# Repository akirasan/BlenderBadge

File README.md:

# BlenderBadge
Una PCB badge basada en el logo de Blender

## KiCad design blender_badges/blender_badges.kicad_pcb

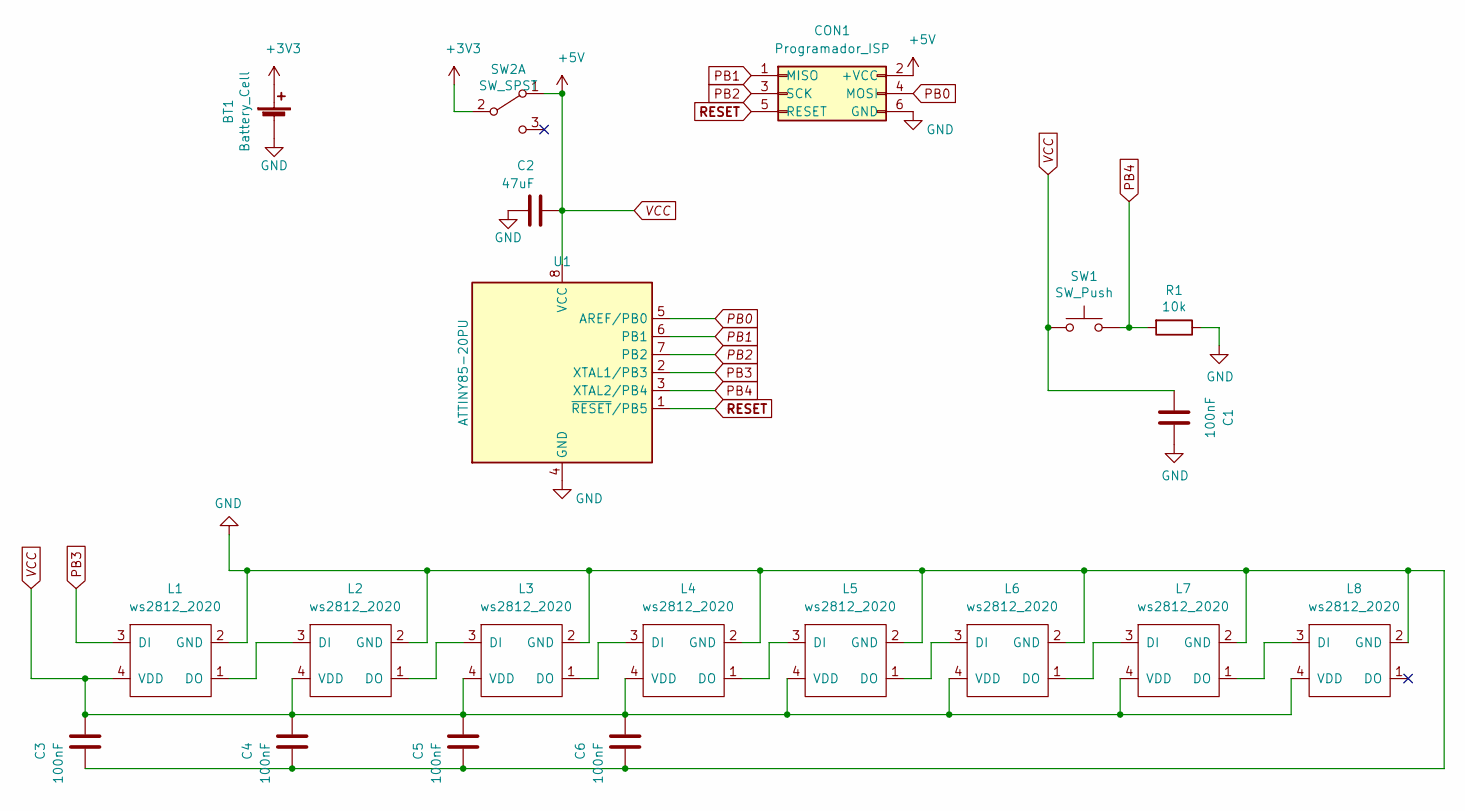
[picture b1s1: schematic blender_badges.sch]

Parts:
BT1: Battery_Cell; BatteryHolder_Keystone_3034_1x20mm_MODIFICADA
C1, C3, C4, C5, C6: 100nF; C_0805_2012Metric_Pad1.15x1.40mm_HandSolder
C2: 47uF; C_0805_2012Metric_Pad1.15x1.40mm_HandSolder
CON1: Programador_ISP; ISP_TestPoints
L1, L2, L3, L4, L5, L6, L7, L8: ws2812_2020
R1: 10k; R_0805_2012Metric_Pad1.15x1.40mm_HandSolder
SW1: SW_Push; SW_SPST_TL3342
SW2: SW_SPST; SWITCH_SPST_SMD_A
U1: ATTINY85-20PU; SOIJ-8_5.3x5.3mm_P1.27mm

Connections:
+3V3: BT1.1 (+), SW2.2 (B)
GND: BT1.2 (-), C1.2, C2.1, C3.1, C4.1, C5.1, C6.1, CON1.6 (GND), L1.2 (GND), L2.2 (GND), L3.2 (GND), L4.2 (GND), L5.2 (GND), L6.2 (GND), L7.2 (GND), L8.2 (GND), R1.1, U1.4 (GND)
unnamed: L1.1 (DO), L2.3 (DI)
unnamed: L2.1 (DO), L3.3 (DI)
unnamed: L3.1 (DO), L4.3 (DI)
unnamed: L4.1 (DO), L5.3 (DI)
unnamed: L5.1 (DO), L6.3 (DI)
unnamed: L6.1 (DO), L7.3 (DI)
unnamed: L7.1 (DO), L8.3 (DI)
PB0: CON1.4 (MOSI), U1.5 (AREF/PB0)
PB1: CON1.1 (MISO), U1.6 (PB1)
PB2: CON1.3 (SCK), U1.7 (PB2)
PB3: L1.3 (DI), U1.2 (XTAL1/PB3)
PB4: R1.2, SW1.2, U1.3 (XTAL2/PB4)
RESET: CON1.5 (RESET), U1.1 (~RESET~/PB5)
VCC: C1.1, C2.2, C3.2, C4.2, C5.2, C6.2, CON1.2 (+VCC), L1.4 (VDD), L2.4 (VDD), L3.4 (VDD), L4.4 (VDD), L5.4 (VDD), L6.4 (VDD), L7.4 (VDD), L8.4 (VDD), SW1.1, SW2.1 (A), U1.8 (VCC)

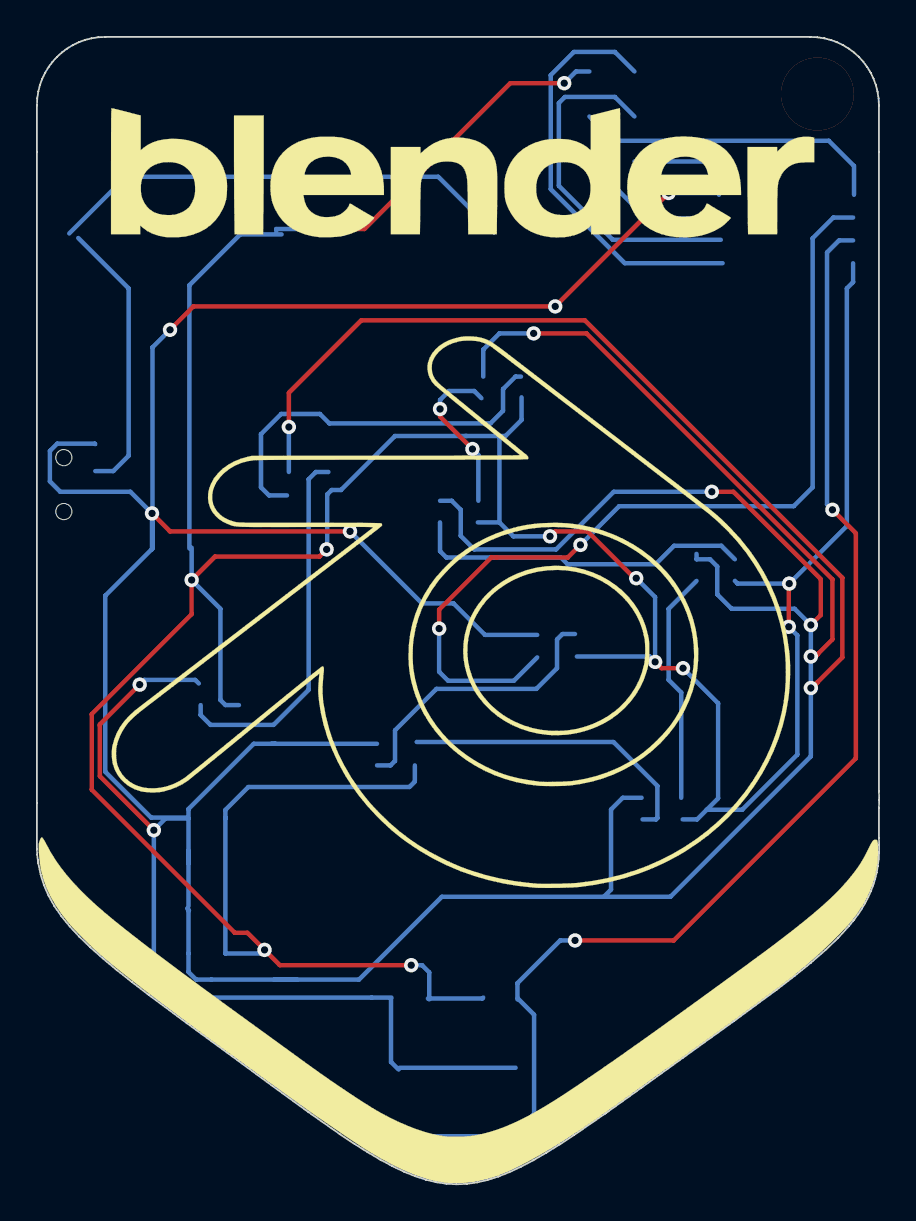
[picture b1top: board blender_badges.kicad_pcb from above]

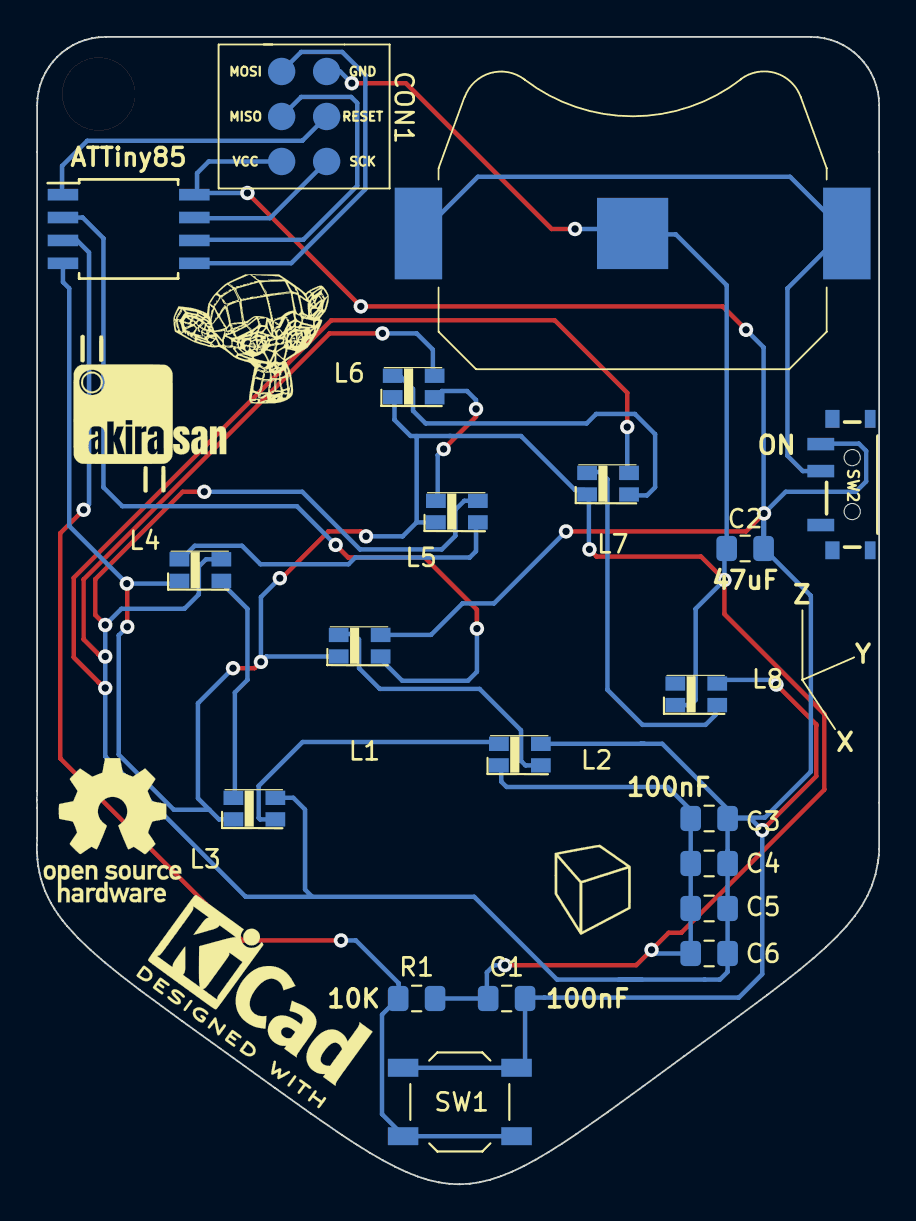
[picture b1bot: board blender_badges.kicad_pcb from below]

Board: 2 copper layers, 46.8 x 63.7 mm, 25 parts (24 on the bottom side), 16 nets.

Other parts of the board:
Ref**: Val**; xyz
Ref**#2: Val**; blender_community_badge
Ref**#3: Val**; suzannie
Ref**#4: Val**; cube
Ref**#5: Val**; akirasan_logo_inv

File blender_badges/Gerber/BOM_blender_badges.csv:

Id,Designator,Package,Quantity,Designation,Supplier and ref
8,"L1,L2,L3,L4,L5,L6,L7,L8",ws2812_2020,8,ws2812_2020,
9,R1,R_0805_2012Metric_Pad1.15x1.40mm_HandSolder,1,10k,
10,U1,SOIJ-8_5.3x5.3mm_P1.27mm,1,ATTINY85-20PU,
11,BT1,BatteryHolder_Keystone_3034_1x20mm_MODIFICADA,1,Battery_Cell,
12,"C1,C3,C4,C5,C6",C_0805_2012Metric_Pad1.15x1.40mm_HandSolder,5,100nF,
13,C2,C_0805_2012Metric_Pad1.15x1.40mm_HandSolder,1,47uF,
14,CON1,ISP_TestPoints,1,Programador_ISP,
15,SW1,SW_SPST_TL3342,1,SW_Push,
16,SW2,SWITCH_SPST_SMD_A,1,SW_SPST,
